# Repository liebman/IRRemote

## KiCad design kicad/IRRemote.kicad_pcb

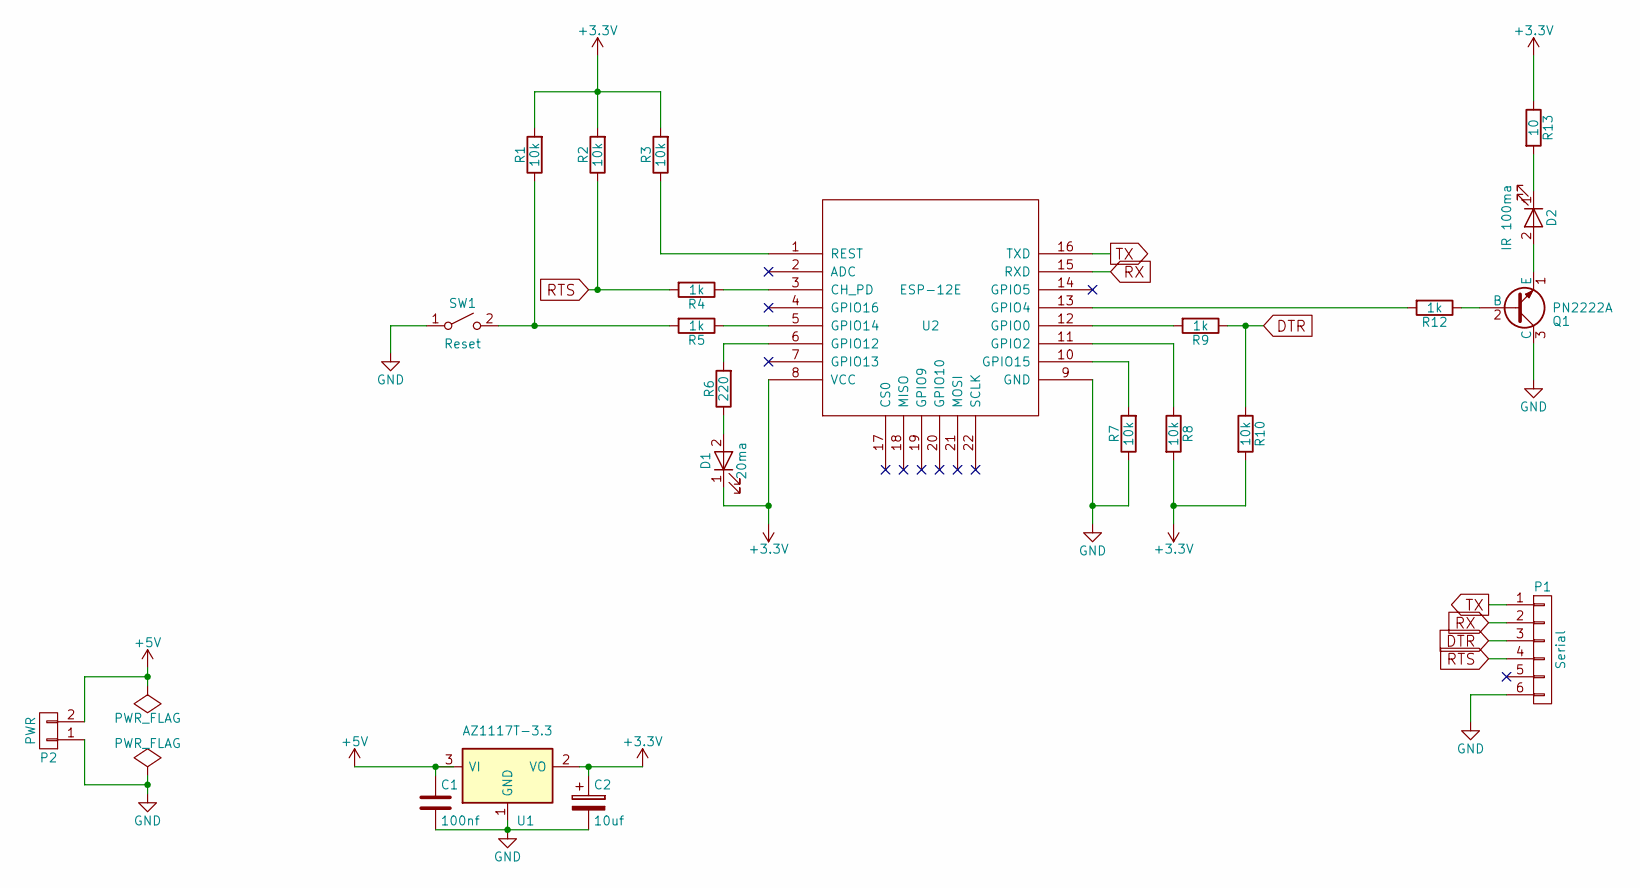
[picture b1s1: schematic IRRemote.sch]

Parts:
C1: 100nf; C_Disc_D3.0mm_W1.6mm_P2.50mm
C2: 10uf; CP_Radial_D4.0mm_P1.50mm
D1: 20ma; Pin_Header_Straight_1x02_Pitch2.54mm
D2: IR 100ma; Pin_Header_Straight_1x02_Pitch2.54mm
P1: Serial; Pin_Header_Straight_1x06_Pitch2.54mm
P2: PWR; Pin_Header_Straight_1x02_Pitch2.54mm
Q1: PN2222A; TO-92_Inline_Wide
R1, R2, R3, R7, R8, R10: 10k; R_Axial_DIN0204_L3.6mm_D1.6mm_P1.90mm_Vertical
R4, R5, R9, R12: 1k; R_Axial_DIN0204_L3.6mm_D1.6mm_P1.90mm_Vertical
R6: 220; R_Axial_DIN0204_L3.6mm_D1.6mm_P1.90mm_Vertical
R13: 10; R_Axial_DIN0204_L3.6mm_D1.6mm_P1.90mm_Vertical
SW1: Reset; SW_PUSH_6mm_h5mm
U1: AZ1117T-3.3; TO-220_Neutral123_Vertical
U2: ESP-12E; ESP8266-12E-EBAY-ADAPTER

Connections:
+3V3: C2.1, D1.1 (K), R1.2, R2.2, R3.2, R8.2, R10.2, R13.1, U1.2 (VO), U2.8 (VCC)
+5V: C1.1, P2.2, U1.3 (VI)
DTR: P1.3, R9.1, R10.1
GND: C1.2, C2.2, P1.6, P2.1, Q1.3 (C), R7.1, SW1.1 (A), U1.1 (GND), U2.9 (GND)
unnamed: D1.2 (A), R6.1
unnamed: D2.1 (K), R13.2
unnamed: D2.2 (A), Q1.1 (E)
unnamed: Q1.2 (B), R12.1
unnamed: R1.1, R5.2, SW1.2 (B)
unnamed: R3.1, U2.1 (REST)
unnamed: R4.1, U2.3 (CH_PD)
unnamed: R5.1, U2.5 (GPIO14)
unnamed: R6.2, U2.6 (GPIO12)
unnamed: R7.2, U2.10 (GPIO15)
unnamed: R8.1, U2.11 (GPIO2)
unnamed: R9.2, U2.12 (GPIO0)
unnamed: R12.2, U2.13 (GPIO4)
RTS: P1.4, R2.1, R4.2
RX: P1.2, U2.15 (RXD)
TX: P1.1, U2.16 (TXD)

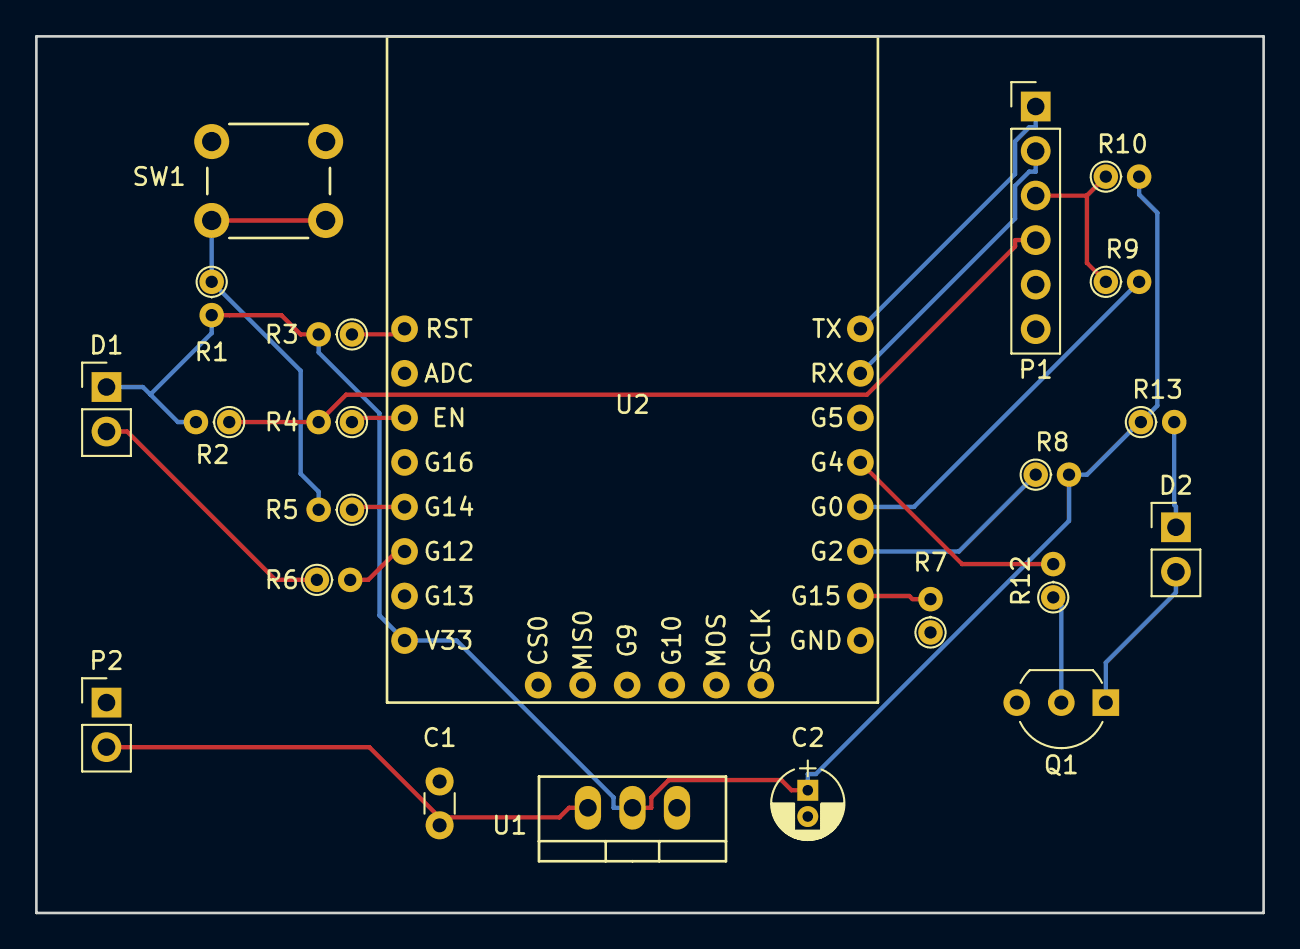
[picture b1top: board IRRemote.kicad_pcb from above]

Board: 2 copper layers, 70.0 x 50.0 mm, 22 parts (0 on the bottom side), 20 nets.

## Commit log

2017-02-05 added kicad design files
